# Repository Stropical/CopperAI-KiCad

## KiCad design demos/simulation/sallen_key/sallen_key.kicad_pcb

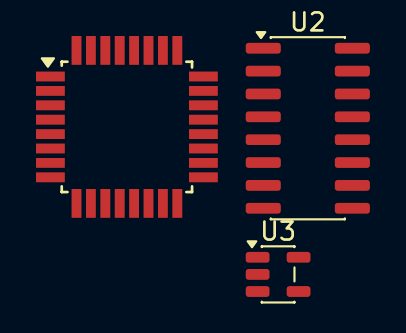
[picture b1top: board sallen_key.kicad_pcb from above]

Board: 2 copper layers, 3 parts (0 on the bottom side), 3 nets, no tracks yet.

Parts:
U1: TQFP-32_7x7mm_P0.8mm
U2: SOIC-16_3.9x9.9mm_P1.27mm
U3: SOT-23-5

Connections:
+3V3: U1.3 (GND), U1.4 (VCC), U1.5 (GND), U1.6 (VCC), U1.18 (AVCC), U1.21 (GND), U1.23 (PC0), U1.24 (PC1), U1.25 (PC2), U2.1 (GND), U2.16 (VCC), U3.1 (VIN), U3.2 (GND), U3.3 (EN), U3.5 (VOUT)
MCU_RXD: U1.30 (PD0), U2.2 (TXD)
MCU_TXD: U1.31 (PD1), U2.3 (RXD)

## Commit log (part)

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2026-05-26 Initial CopperAI KiCad source release
2026-05-29 Fix Windows installer branding and agent pane
2026-05-29 Darken Windows frame chrome
2026-05-29 Darken remaining Windows chrome
2026-05-29 Darken native Windows menu and status chrome
2026-05-29 Enable Win32 dark menu mode earlier
2026-05-29 Paint native Windows menu bar dark
2026-05-29 Remove remaining native white chrome
2026-05-29 fix: enable CopperAI native KiCad webview IPC
2026-05-30 Fix Windows WebView IPC build
2026-05-30 Use KiCad JSON wrapper in WebView panel
2026-05-30 Fix Windows auth callback and native dark seams
2026-05-30 Include UI colors for dark notebook art
2026-05-30 Fix WebView2 message dispatch and hide toolbar gap
2026-05-30 Handle Copper host RPC messages in WebView
2026-05-30 Polish agent tabs and hide top chrome seam
2026-05-30 Track Windows MSI generator with app launch
2026-05-30 Darken paged preferences dialogs
2026-06-02 Darken AUI pane borders
2026-06-02 Apply dark theme to generated windows
2026-06-02 Avoid HTML include in Windows dark theme helper
2026-06-02 Guard Windows headers for dark theme controls
2026-06-02 Fix batch schematic component placement
2026-06-02 Fix-Windows-MCP-server-compatibility
2026-06-02 Fix Windows dark menu seam and tree border
2026-06-02 Darken native wxMSW controls
2026-06-02 Reduce component search UI stalls
2026-06-03 Optimize search components and webview bridge
2026-06-03 Optimize component search on Windows
2026-06-03 Fix component search freeze on Windows
2026-06-11 ci: download release RPM via browser_download_url (the API asset url returned a 1.7KB redirect stub, not the binary); assert size+file type
